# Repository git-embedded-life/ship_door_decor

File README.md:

# ship_door_decor
Magnetic ship door decor that uses an ESP32 to animate a light strip to illuminate the background

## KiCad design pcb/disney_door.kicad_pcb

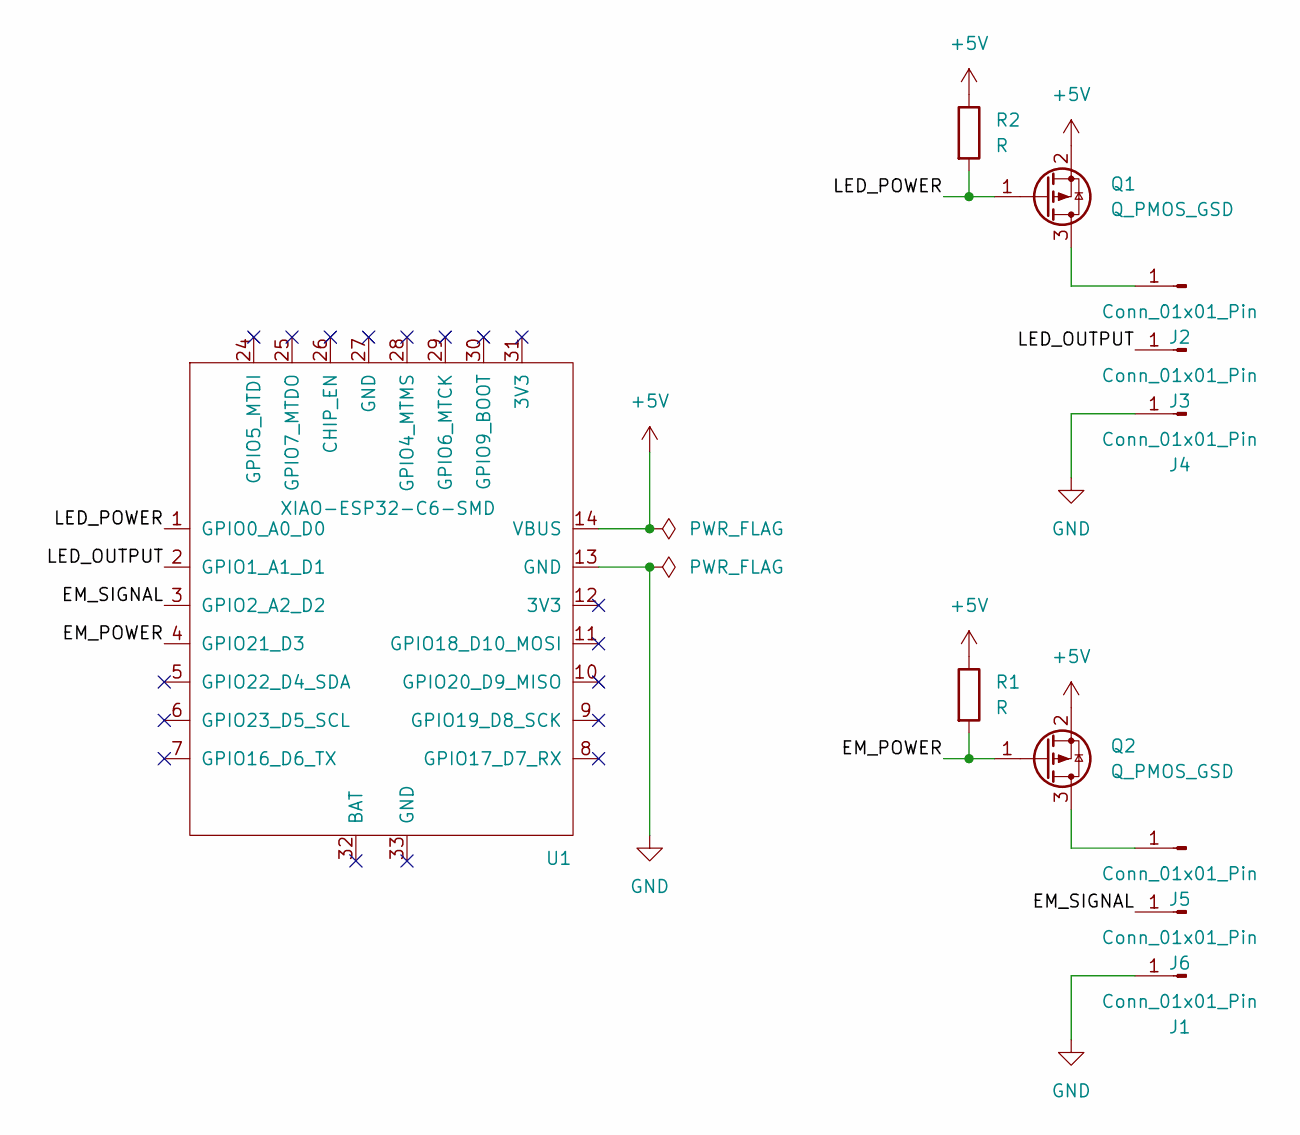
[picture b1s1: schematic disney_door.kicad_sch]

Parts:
J1, J2, J3, J4, J5, J6: Conn_01x01_Pin; SolderWirePad_1x01_SMD_2x4mm
Q1, Q2: Q_PMOS_GSD; SOT-23-3
R1, R2: R; R_0805_2012Metric
U1: XIAO-ESP32-C6-SMD

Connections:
+5V: Q1.2 (S), Q2.2 (S), R1.1, R2.1, U1.14 (VBUS)
/EM_POWER: Q2.1 (G), R1.2, U1.4 (GPIO21_D3)
/EM_SIGNAL: J6.1 (Pin_1_1), U1.3 (GPIO2_A2_D2)
/LED_OUTPUT: J3.1 (Pin_1_1), U1.2 (GPIO1_A1_D1)
/LED_POWER: Q1.1 (G), R2.2, U1.1 (GPIO0_A0_D0)
GND: J1.1 (Pin_1_1), J4.1 (Pin_1_1), U1.13 (GND)
unnamed: J2.1 (Pin_1_1), Q1.3 (D)
unnamed: J5.1 (Pin_1_1), Q2.3 (D)

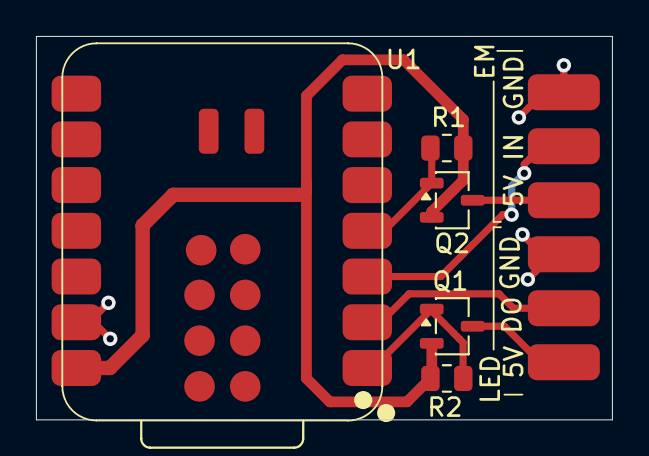
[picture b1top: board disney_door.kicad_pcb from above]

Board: 2 copper layers, 32.0 x 21.3 mm, 11 parts (0 on the bottom side), 8 nets.
